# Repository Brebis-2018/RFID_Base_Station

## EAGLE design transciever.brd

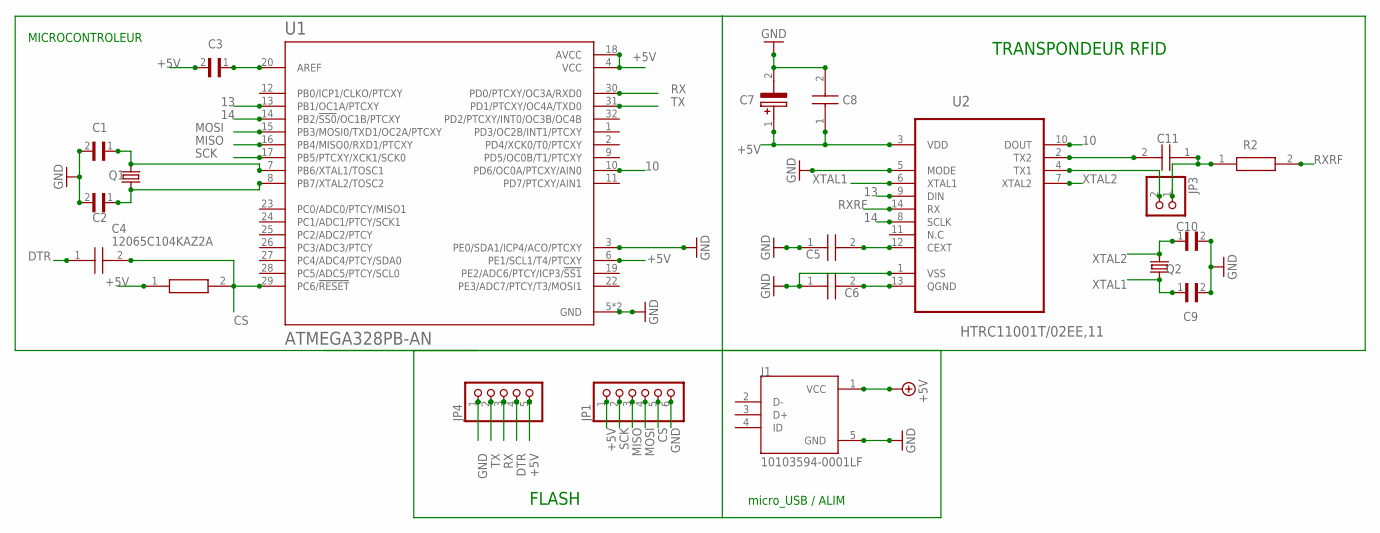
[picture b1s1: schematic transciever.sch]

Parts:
C1, C2, C9, C10: 06031U220GAT2A; CAPC1608X90
C3: GRT31CC80J476KE13L; CAP3216X125N
C4, C5, C6, C8, C11: 12065C104KAZ2A; CAPC3216X94N
C7: NACE100M16V4X5.5TR13F; NACE(4X5.5)
J1: 10103594-0001LF; FCI_10103594-0001LF
JP1: PINHD-1X6; 1X06
JP3: PINHD-1X2; 1X02
JP4: PINHD-1X5; 1X05
Q1, Q2: KX-K; 11.4X4.5
R1, R2: CRCW12061K00FKEA; RESC3216X60N
U1: ATMEGA328PB-AN; QFP80P900X900X120-32N
U2: HTRC11001T/02EE,11; SOIC127P600X175-14N

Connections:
10: U1.10 (PD6/OC0A/PTCXY/AIN0), U2.10 (DOUT)
13: U1.13 (PB1/OC1A/PTCXY), U2.9 (DIN)
14: U1.14 (PB2/!SS0!/OC1B/PTCXY), U2.8 (SCLK)
+5V: C3.2, C7.1 (+), C8.1, J1.1 (VCC), JP1.1, JP4.5, R1.1, U1.4 (VCC), U1.6 (PE1/SCL1/T4/PTCXY), U1.18 (AVCC), U2.3 (VDD)
CS: C4.2, JP1.5, R1.2, U1.29 (PC6/!RESET)
DTR: C4.1, JP4.4
GND: C1.2, C2.2, C5.1, C6.1, C7.2 (-), C8.2, C9.2, C10.2, J1.5 (GND), JP1.6, JP4.1, U1.3 (PE0/SDA1/ICP4/ACO/PTCXY), U1.5 (GND), U1.21 (GND), U2.1 (VSS), U2.5 (MODE)
MISO: JP1.3, U1.16 (PB4/MISO0/RXD1/PTCXY)
MOSI: JP1.4, U1.15 (PB3/MOSI0/TXD1/OC2A/PTCXY)
unnamed: C1.1, Q1.2, U1.7 (PB6/XTAL1/TOSC1)
unnamed: C2.1, Q1.1, U1.8 (PB7/XTAL2/TOSC2)
unnamed: C3.1, U1.20 (AREF)
unnamed: C11.2, U2.2 (TX2)
unnamed: C5.2, U2.12 (CEXT)
unnamed: C11.1, JP3.1, R2.1
unnamed: C6.2, U2.13 (QGND)
unnamed: JP3.2, U2.4 (TX1)
RX: JP4.3, U1.30 (PD0/PTCXY/OC3A/RXD0)
RXRF: R2.2, U2.14 (RX)
SCK: JP1.2, U1.17 (PB5/PTCXY/XCK1/SCK0)
TX: JP4.2, U1.31 (PD1/PTCXY/OC4A/TXD0)
XTAL1: C9.1, Q2.2, U2.6 (XTAL1)
XTAL2: C10.1, Q2.1, U2.7 (XTAL2)

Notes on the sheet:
FLASH
micro_USB / ALIM
TRANSPONDEUR RFID
MICROCONTROLEUR

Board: 2 copper layers, 21 parts (0 on the bottom side), 23 nets, no tracks yet.

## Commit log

2018-06-29 push inital Sch V1.0

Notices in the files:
parts and their libraries:
crystal-geyer_V1_0: Copyright: Geyer-Electronic
